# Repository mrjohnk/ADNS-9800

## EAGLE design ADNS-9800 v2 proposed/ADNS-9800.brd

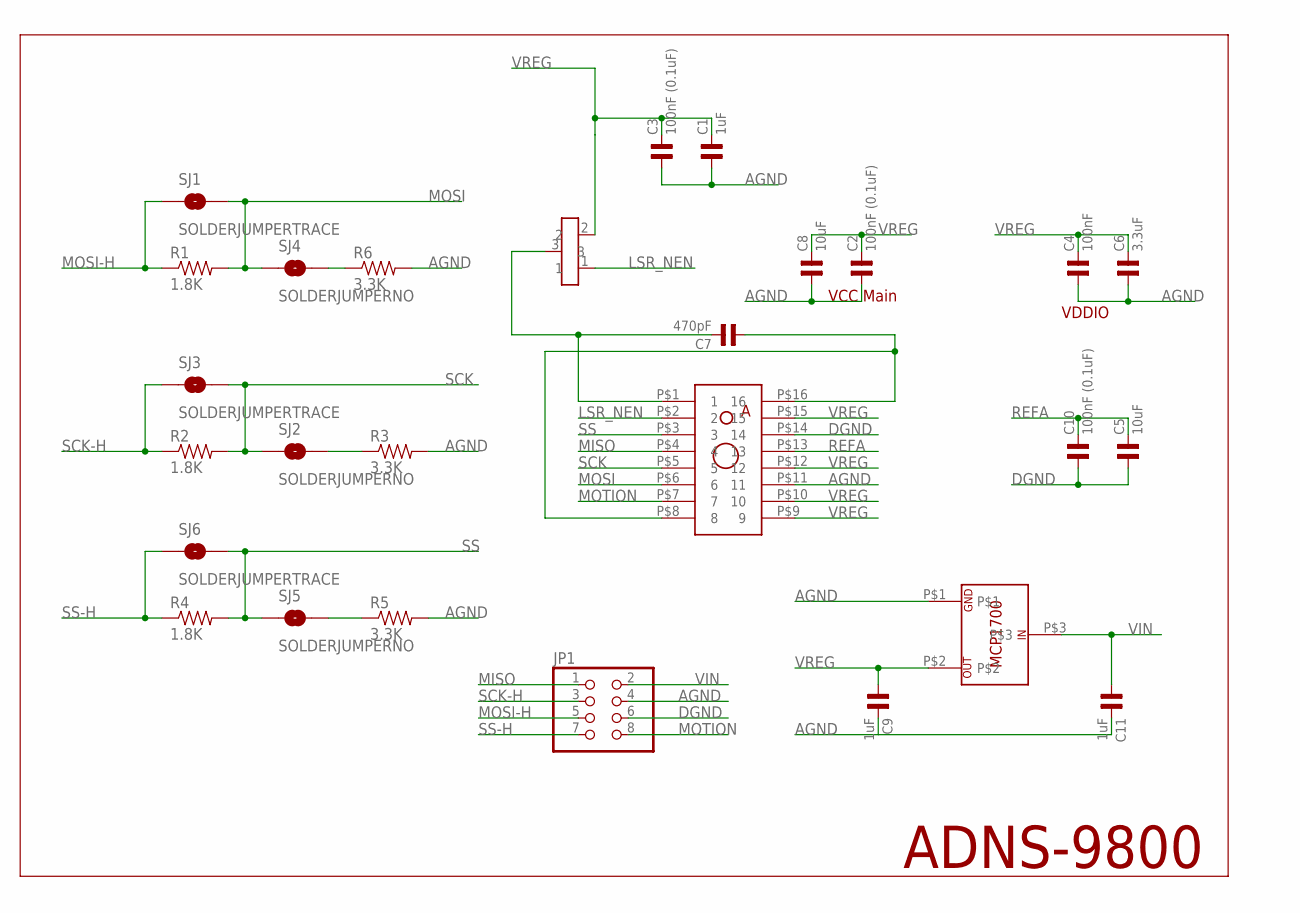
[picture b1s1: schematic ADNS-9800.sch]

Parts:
C1, C9, C11: 1uF; 0603
C2, C3, C10: 100nF (0.1uF); 0603
C4: 100nF; 0603
C5, C8: 10uF; 0603
C6: 3.3uF; 0603
C7: 470pF; 0603
JP1: PINHD-2X4; 2X04
Q1: TRANSISTOR_SC-75; SC-75_TRANSISTOR
R1, R2, R4: 1.8K; 0603-RES
R3, R5, R6: 3.3K; 0603-RES
SJ1, SJ3, SJ6: SOLDERJUMPERTRACE; SJ_2S-TRACE
SJ2, SJ4, SJ5: SOLDERJUMPERNO; SJ_2S-NO
U$1: AVAGO_ADNS-9500
U$2: MCP1700__LDO

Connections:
AGND: C1.1, C2.1, C3.1, C4.1, C6.1, C8.1, C9.2, C11.2, JP1.4, R3.2, R5.2, R6.2, U$1.P$11 (11), U$2.P$1
DGND: C5.1, C10.1, JP1.6, U$1.P$14 (14)
LSR_NEN: Q1.1, U$1.P$2 (2)
MISO: JP1.1, U$1.P$4 (4)
MOSI: R1.2, SJ1.2, SJ4.1, U$1.P$6 (6)
MOSI-H: JP1.5, R1.1, SJ1.1
MOTION: JP1.8, U$1.P$7 (7)
unnamed: C7.1, U$1.P$8 (8), U$1.P$16 (16)
unnamed: C7.2, Q1.3, U$1.P$1 (1)
unnamed: R6.1, SJ4.2
unnamed: R3.1, SJ2.2
unnamed: R5.1, SJ5.2
REFA: C5.2, C10.2, U$1.P$13 (13)
SCK: R2.2, SJ2.1, SJ3.2, U$1.P$5 (5)
SCK-H: JP1.3, R2.1, SJ3.1
SS: R4.2, SJ5.1, SJ6.2, U$1.P$3 (3)
SS-H: JP1.7, R4.1, SJ6.1
VIN: C11.1, JP1.2, U$2.P$3
VREG: C1.2, C2.2, C3.2, C4.2, C6.2, C8.2, C9.1, Q1.2, U$1.P$9 (9), U$1.P$10 (10), U$1.P$12 (12), U$1.P$15 (15), U$2.P$2

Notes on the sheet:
ADNS-9800
VDDIO
VCC Main

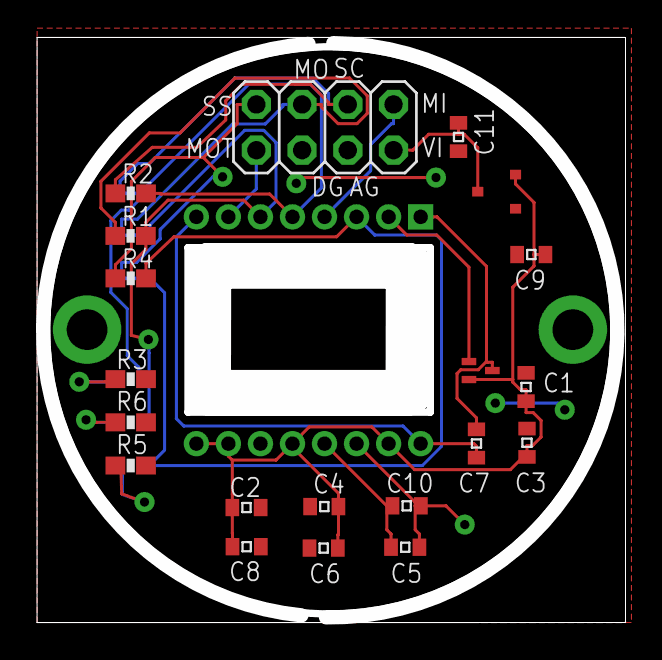
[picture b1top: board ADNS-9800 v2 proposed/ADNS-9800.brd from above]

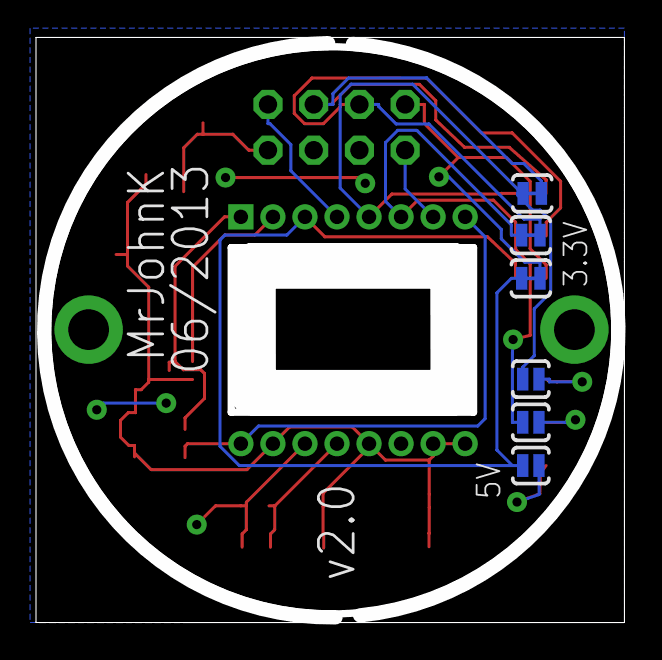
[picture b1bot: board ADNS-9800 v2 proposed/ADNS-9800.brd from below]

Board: 2 copper layers, 32.7 x 32.5 mm, 27 parts (6 on the bottom side), 19 nets.

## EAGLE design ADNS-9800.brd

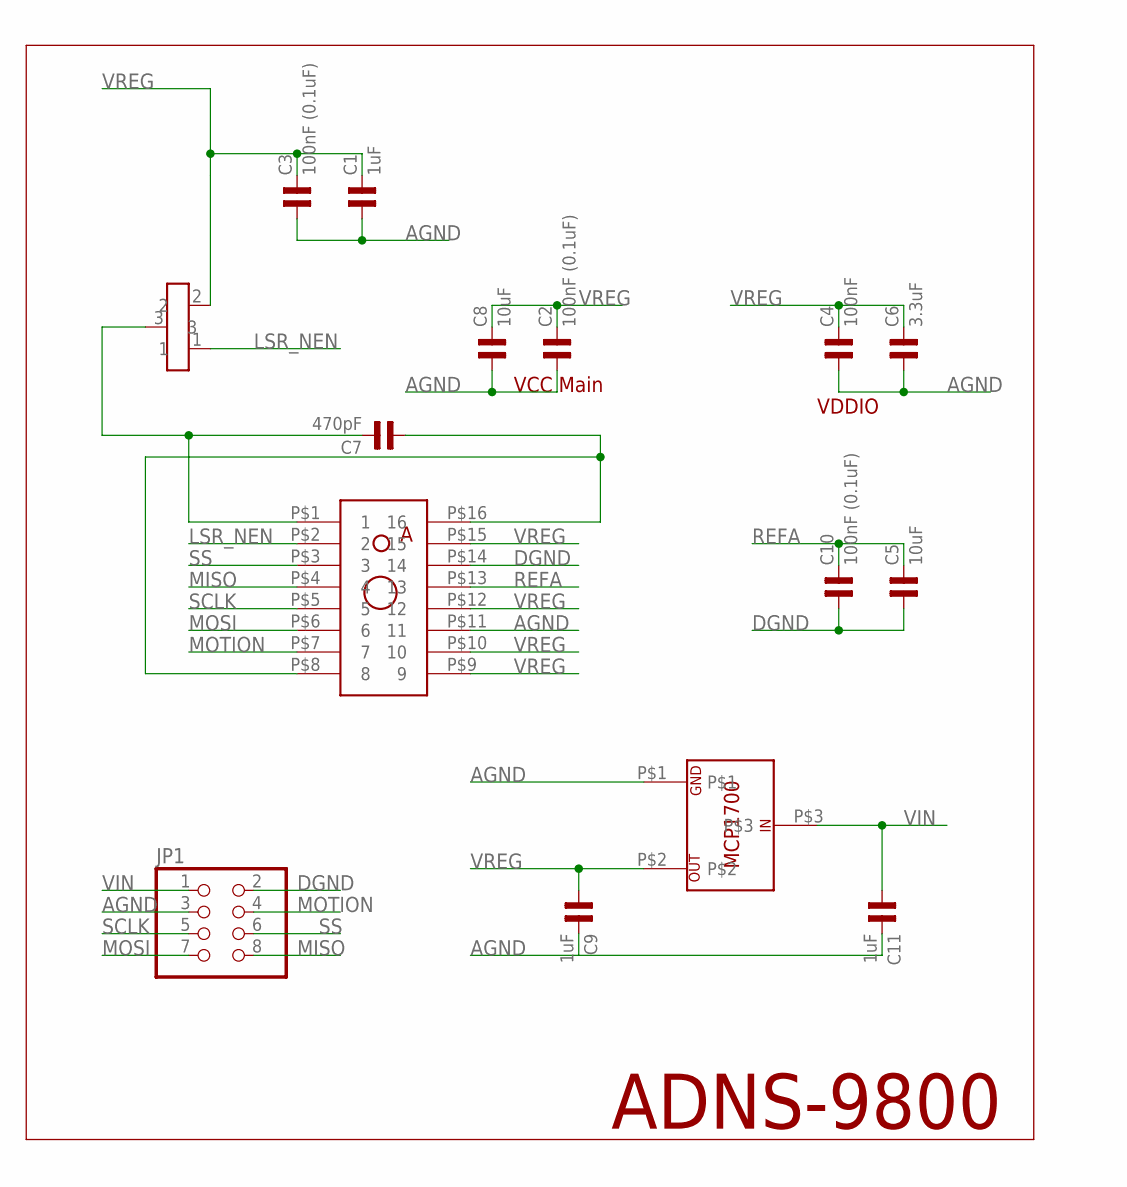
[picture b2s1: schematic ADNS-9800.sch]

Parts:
C1, C9, C11: 1uF; 0603
C2, C3, C10: 100nF (0.1uF); 0603
C4: 100nF; 0603
C5, C8: 10uF; 0603
C6: 3.3uF; 0603
C7: 470pF; 0603
JP1: PINHD-2X4; 2X04
Q1: TRANSISTOR_SC-75; SC-75_TRANSISTOR
U$1: AVAGO_ADNS-9500
U$2: MCP1700__LDO

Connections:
AGND: C1.1, C2.1, C3.1, C4.1, C6.1, C8.1, C9.2, C11.2, JP1.3, U$1.P$11 (11), U$2.P$1
DGND: C5.1, C10.1, JP1.2, U$1.P$14 (14)
LSR_NEN: Q1.1, U$1.P$2 (2)
MISO: JP1.8, U$1.P$4 (4)
MOSI: JP1.7, U$1.P$6 (6)
MOTION: JP1.4, U$1.P$7 (7)
unnamed: C7.1, U$1.P$8 (8), U$1.P$16 (16)
unnamed: C7.2, Q1.3, U$1.P$1 (1)
REFA: C5.2, C10.2, U$1.P$13 (13)
SCLK: JP1.5, U$1.P$5 (5)
SS: JP1.6, U$1.P$3 (3)
VIN: C11.1, JP1.1, U$2.P$3
VREG: C1.2, C2.2, C3.2, C4.2, C6.2, C8.2, C9.1, Q1.2, U$1.P$9 (9), U$1.P$10 (10), U$1.P$12 (12), U$1.P$15 (15), U$2.P$2

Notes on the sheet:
ADNS-9800
VDDIO
VCC Main

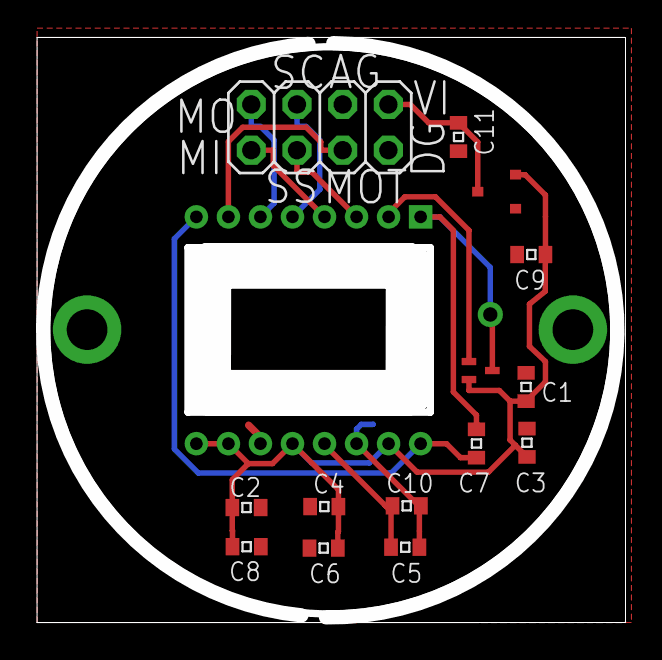
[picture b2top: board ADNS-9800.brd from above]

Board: 2 copper layers, 32.7 x 32.5 mm, 15 parts (0 on the bottom side), 13 nets.

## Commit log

2013-04-27 ADNS-9800 test code
    test code for hooking an ADNS-9800 to a Teensy via Teesnyduino
2013-05-22 Adding Eagle design files
2013-05-29 Bill of Materials
2013-06-15 version 2 proposed design
2013-06-15 V2 Design
2013-06-18 v2 w/5V Support
2013-07-20 Arduino Pro Mini test with serial output
2013-08-24 Corrected missing trace. Removed unnecessary via
2014-03-27 Alternate Firmware Images
2014-04-19 Arduino non-interrupt based test
2014-05-25 Arduino Sketch
2016-03-16 Updated variable declarations
    updated variable declarations to match changes in Arduino
2019-06-10 Update firmware_data[] type to solve Arduino issue
2019-06-10 Update firmware_data[] type
    Solve issue with Arduino compiling
2019-06-10 Update firmware_data[] type
    To solve Arduino compiling issue

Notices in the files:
parts and their libraries:
SparkFun-Passives: Licensing: CC v3.0 Share-Alike You are welcome to use this library for commercial purposes.
